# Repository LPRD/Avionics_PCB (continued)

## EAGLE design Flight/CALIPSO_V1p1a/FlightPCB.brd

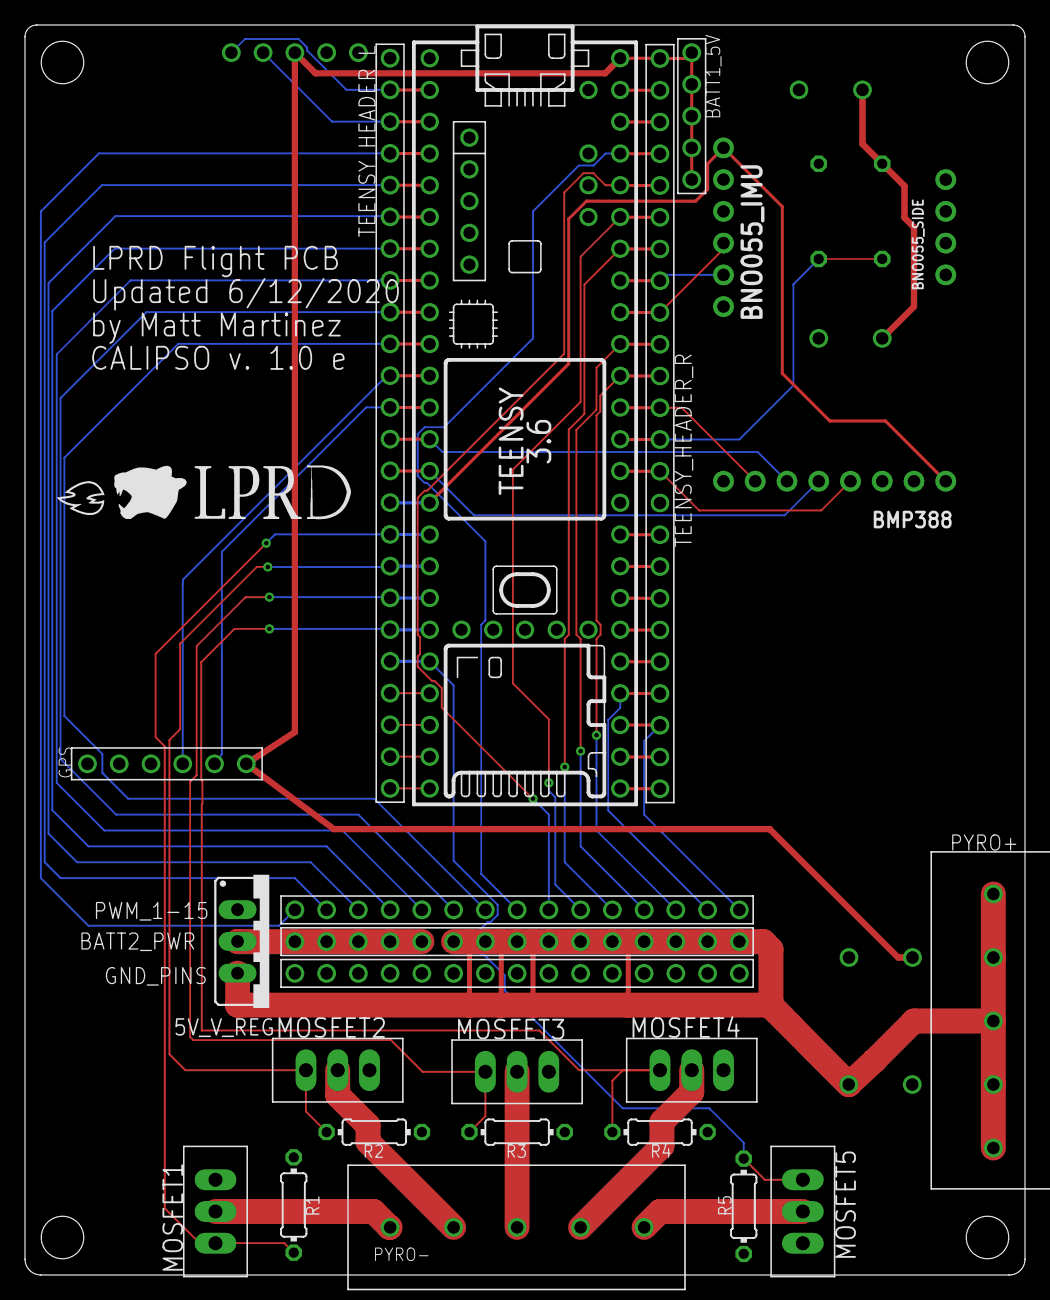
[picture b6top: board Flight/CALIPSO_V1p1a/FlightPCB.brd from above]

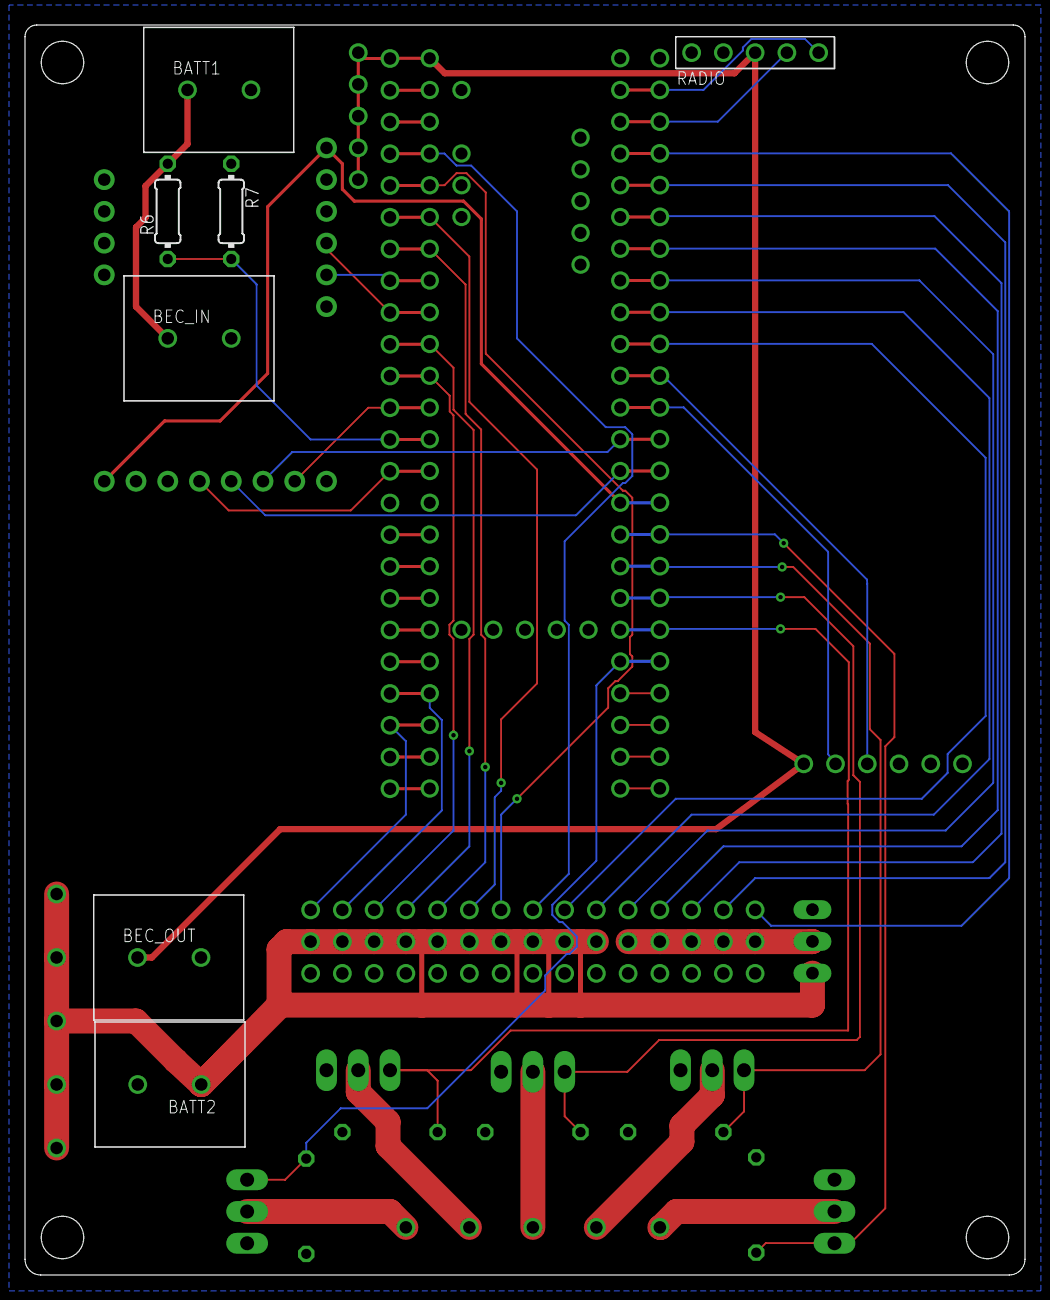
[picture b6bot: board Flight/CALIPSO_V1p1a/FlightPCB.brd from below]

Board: 2 copper layers, 80.0 x 100.0 mm, 31 parts (7 on the bottom side), 55 nets.

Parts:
5V_V_REG: LM1086TO220V; TO220S
BATT1: 2-4S LIPO; TERMINAL_BLOCK_2_PIN_5MM
BATT1_5V: PIN_HEADER_5
BATT2: 2-6S LIPO (>5.6V); TERMINAL_BLOCK_2_PIN_5MM
BATT2_PWR: 1-10=Batt2, 11-15=5V Reg; PIN_HEADER_15
BEC_IN: TERMINAL_BLOCK_2_PIN_5MM
BEC_OUT: TERMINAL_BLOCK_2_PIN_5MM
BMP388: MICROBUILDER_1X08_ROUND
BNO055_IMU: MICROBUILDER_1X06_ROUND
BNO055_SIDE: MICROBUILDER_1X04_ROUND
FLIGHT_COMPUTER: TEENSY_3.5/3.6
GND_PINS: PIN_HEADER_15
GPS: NEO_M8N_GPS_BREAKOUT
MOSFET1, MOSFET2, MOSFET3, MOSFET4, MOSFET5: IRLZ44Z; TO220BH_SIMPLE
PWM_1-15: PIN_HEADER_15
PYRO+: TERMINAL_BLOCK_5_PIN_5MM
PYRO-: TERMINAL_BLOCK_5_PIN_5MM
R1, R2, R3, R4, R5, R6: 10k; 0204/7
R7: 2k; 0204/7
RADIO: RFD900
TEENSY_HEADER_L: PIN_HEADER_24_TEENSY_RAIL
TEENSY_HEADER_R: PIN_HEADER_24_TEENSY_RAIL

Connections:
+3V3: BMP388.1, BNO055_IMU.6, FLIGHT_COMPUTER.3V3, TEENSY_HEADER_L.P10
+5V: BATT1_5V.P1, BATT1_5V.P2, BATT1_5V.P3, BATT1_5V.P4, BATT1_5V.P5, BEC_OUT.P1, FLIGHT_COMPUTER.VIN, GPS.P6, RADIO.3, TEENSY_HEADER_R.P1
+5V/1: 5V_V_REG.2, BATT2_PWR.P11, BATT2_PWR.P12, BATT2_PWR.P13, BATT2_PWR.P14, BATT2_PWR.P15
BATT1_READ_V: FLIGHT_COMPUTER.14/A0, R6.1, R7.2, TEENSY_HEADER_R.P13
BATT1_VCC: BATT1.P1, BEC_IN.P1, R6.2
BMP388_CS0: BMP388.7, FLIGHT_COMPUTER.15/A1, TEENSY_HEADER_R.P12
BMP388_SCK: BMP388.4, FLIGHT_COMPUTER.13/SCK, TEENSY_HEADER_R.P14
BMP388_SDI/MOSI: BMP388.6, FLIGHT_COMPUTER.11/MOSI, TEENSY_HEADER_L.P12
BMP388_SDO/MISO: BMP388.5, FLIGHT_COMPUTER.12/MISO, TEENSY_HEADER_L.P11
BNO055_SCL: BNO055_IMU.2, FLIGHT_COMPUTER.19/A5/SCL, TEENSY_HEADER_R.P8
BNO055_SDA: BNO055_IMU.3, FLIGHT_COMPUTER.18/A4/SDA, TEENSY_HEADER_R.P9
CH1: MOSFET1.D, PYRO-.P1
CH2: MOSFET2.D, PYRO-.P2
CH3: MOSFET3.D, PYRO-.P3
CH4: MOSFET4.D, PYRO-.P4
CH5: MOSFET5.D, PYRO-.P5
GND: 5V_V_REG.1, BATT1.P2, BATT2.P2, BEC_IN.P2, BEC_OUT.P2, BMP388.3, BNO055_IMU.4, FLIGHT_COMPUTER.GND, FLIGHT_COMPUTER.GND2, GND_PINS.P1, GND_PINS.P2, GND_PINS.P3, GND_PINS.P4, GND_PINS.P5, GND_PINS.P6, GND_PINS.P7, GND_PINS.P8, GND_PINS.P9, GND_PINS.P10, GND_PINS.P11, GND_PINS.P12, GND_PINS.P13, GND_PINS.P14, GND_PINS.P15, GPS.P1, MOSFET1.S, MOSFET2.S, MOSFET3.S, MOSFET4.S, MOSFET5.S, R1.2, R2.2, R3.2, R4.2, R5.2, R7.1, RADIO.1, TEENSY_HEADER_L.P24, TEENSY_HEADER_R.P15
GPS_RX: FLIGHT_COMPUTER.10/CS, GPS.P5, TEENSY_HEADER_L.P13
GPS_TX: FLIGHT_COMPUTER.9/CS, GPS.P4, TEENSY_HEADER_L.P14
unnamed: FLIGHT_COMPUTER.AGND, TEENSY_HEADER_R.P2
unnamed: FLIGHT_COMPUTER.3V3_LO, TEENSY_HEADER_R.P3
unnamed: FLIGHT_COMPUTER.32/A13, TEENSY_HEADER_L.P1
unnamed: FLIGHT_COMPUTER.31/A12, TEENSY_HEADER_L.P2
unnamed: FLIGHT_COMPUTER.30, TEENSY_HEADER_L.P3
unnamed: FLIGHT_COMPUTER.29, TEENSY_HEADER_L.P4
unnamed: FLIGHT_COMPUTER.A22/DAC1, TEENSY_HEADER_R.P16
unnamed: FLIGHT_COMPUTER.21/DAC0, TEENSY_HEADER_R.P17
unnamed: FLIGHT_COMPUTER.39/A20, TEENSY_HEADER_R.P18
unnamed: FLIGHT_COMPUTER.38/A19, TEENSY_HEADER_R.P19
unnamed: FLIGHT_COMPUTER.37/A18, TEENSY_HEADER_R.P20
unnamed: FLIGHT_COMPUTER.34/A15, TEENSY_HEADER_R.P23
unnamed: FLIGHT_COMPUTER.33/A14, TEENSY_HEADER_R.P24
PWM2/3: FLIGHT_COMPUTER.3/CANTX, PWM_1-15.P2, TEENSY_HEADER_L.P20
PWM3/4: FLIGHT_COMPUTER.4/CANRX, PWM_1-15.P3, TEENSY_HEADER_L.P19
PWM4/5: FLIGHT_COMPUTER.5, PWM_1-15.P4, TEENSY_HEADER_L.P18
PWM5/6: FLIGHT_COMPUTER.6, PWM_1-15.P5, TEENSY_HEADER_L.P17
PWM6/7: FLIGHT_COMPUTER.7, PWM_1-15.P6, TEENSY_HEADER_L.P16
PWM7/8: FLIGHT_COMPUTER.8, PWM_1-15.P7, TEENSY_HEADER_L.P15
PWM8/23/A9: FLIGHT_COMPUTER.23/A9, PWM_1-15.P8, TEENSY_HEADER_R.P4
PWM9/22/A8: FLIGHT_COMPUTER.22/A8, PWM_1-15.P9, TEENSY_HEADER_R.P5
PWM10/21/A7: FLIGHT_COMPUTER.21/A7, PWM_1-15.P10, TEENSY_HEADER_R.P6
PWM11/20/A6: FLIGHT_COMPUTER.20/A6, PWM_1-15.P11, TEENSY_HEADER_R.P7
PWM12/17/A3: FLIGHT_COMPUTER.17/A3, PWM_1-15.P12, TEENSY_HEADER_R.P10
PWM13/16/A2: FLIGHT_COMPUTER.16/A2, PWM_1-15.P13, TEENSY_HEADER_R.P11
PWM14/36/A17: FLIGHT_COMPUTER.36/A17, PWM_1-15.P14, TEENSY_HEADER_R.P21
PWM15/35/A16: FLIGHT_COMPUTER.35/A16, PWM_1-15.P15, TEENSY_HEADER_R.P22
PWN1/2: FLIGHT_COMPUTER.2, PWM_1-15.P1, TEENSY_HEADER_L.P21
PYRO1: FLIGHT_COMPUTER.24, MOSFET1.G, R1.1, TEENSY_HEADER_L.P9
PYRO2: FLIGHT_COMPUTER.25, MOSFET2.G, R2.1, TEENSY_HEADER_L.P8
PYRO3: FLIGHT_COMPUTER.26, MOSFET3.G, R3.1, TEENSY_HEADER_L.P7
PYRO4: FLIGHT_COMPUTER.27, MOSFET4.G, R4.1, TEENSY_HEADER_L.P6
PYRO5: FLIGHT_COMPUTER.28, MOSFET5.G, R5.1, TEENSY_HEADER_L.P5
RADIO_RX: FLIGHT_COMPUTER.1/TX, RADIO.4, TEENSY_HEADER_L.P22
RADIO_TX: FLIGHT_COMPUTER.0/RX, RADIO.5, TEENSY_HEADER_L.P23
VCC: 5V_V_REG.3, BATT2.P1, BATT2_PWR.P1, BATT2_PWR.P2, BATT2_PWR.P3, BATT2_PWR.P4, BATT2_PWR.P5, BATT2_PWR.P6, BATT2_PWR.P7, BATT2_PWR.P8, BATT2_PWR.P9, BATT2_PWR.P10, PYRO+.P1, PYRO+.P2, PYRO+.P3, PYRO+.P4, PYRO+.P5

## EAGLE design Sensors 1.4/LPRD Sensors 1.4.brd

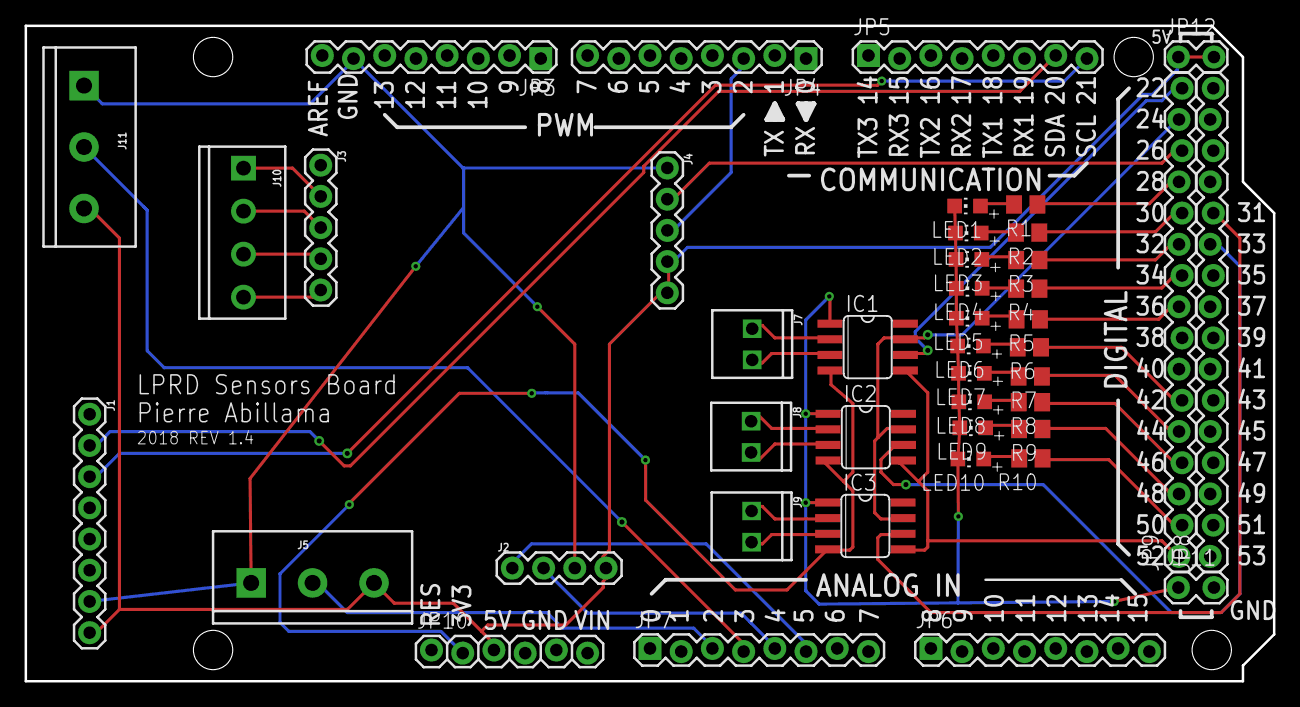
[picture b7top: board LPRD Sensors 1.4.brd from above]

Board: 2 copper layers, 101.6 x 53.3 mm, 45 parts (0 on the bottom side), 46 nets.

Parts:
IC1, IC2, IC3: MAX31855; SO08
J1: 1X08
J2: 1X04
J3, J4: 1X05
J5, J11: SCREWTERMINAL-5MM-3
J7, J8, J9: 1X02_2.54_SCREWTERM
J10: SCREWTERMINAL-3.5MM-4
JP3, JP4, JP5, JP6, JP7: 1X08_LOCK
JP8, JP9: M16LOCK; 1X16_LOCK
JP10: 1X06_LOCK
JP11, JP12: 1X02_LOCK
LED1, LED2, LED3, LED4, LED5, LED6, LED7, LED8, LED9, LED10: CHIP-LED0805
R1, R2, R3, R4, R5, R6, R7, R8, R9, R10: 1000; R0805
U$1: UMNLOGO
U$2: LPRDLOGO

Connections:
3.3V: IC1.4, IC2.4, IC3.4, JP10.2
5V: J1.8, J2.4, J4.4, J4.5, J5.3, J11.3, JP10.3, JP12.1, JP12.2
A+/GREEN: J3.2, J10.1
A-/WHITE: J3.3, J10.2
E+/RED: J3.5, J10.4
E-/BLACK: J3.4, J10.3
FORCE_CLK: J4.2, JP9.14
FORCE_DAT: J4.3, JP4.3
FORCE_LED: JP9.10, R4.1
GND: IC1.1, IC2.1, IC3.1, J1.7, J2.3, J4.1, J5.1, J11.1, JP3.7, JP10.4, JP10.5, JP11.1, JP11.2, LED1.C, LED2.C, LED3.C, LED4.C, LED5.C, LED6.C, LED7.C, LED8.C, LED9.C, LED10.C
MAXCLK: IC1.5, IC2.5, IC3.5, JP9.1
MAXCS1: IC1.6, JP9.16
MAXCS2: IC2.6, JP8.11
MAXCS3: IC3.6, JP8.12
MAXDO: IC1.7, IC2.7, IC3.7, JP9.15
unnamed: LED1.A, R1.2
unnamed: LED2.A, R2.2
unnamed: LED3.A, R3.2
unnamed: LED4.A, R4.2
unnamed: LED5.A, R5.2
unnamed: LED6.A, R6.2
unnamed: LED7.A, R7.2
unnamed: IC1.2, J7.P2
unnamed: IC1.3, J7.P1
unnamed: IC2.2, J8.P2
unnamed: IC2.3, J8.P1
unnamed: IC3.2, J9.P2
unnamed: IC3.3, J9.P1
unnamed: LED8.A, R8.2
unnamed: LED9.A, R9.2
unnamed: LED10.A, R10.2
PRESSURE1_LED: JP9.9, R5.1
PRESSURE2_LED: JP9.2, R10.1
SCL: J1.3, JP5.8
SDA: J1.2, JP5.7
STATE_LED: JP9.6, R6.1
STATUS_LED: JP9.5, R7.1
TEMP1_LED: JP9.4, R8.1
TEMP2_LED: JP9.3, R9.1
THERMO1_LED: JP9.13, R1.1
THERMO2_LED: JP9.12, R2.1
THERMO3_LED: JP9.11, R3.1
VOUT_PRESSURE_1: J5.2, JP7.3
VOUT_PRESSURE_2: J11.2, JP7.4
VOUT_TEMPERATURE_1: J2.2, JP7.5
VOUT_TEMPERATURE_2: J2.1, JP7.6

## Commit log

2018-04-09 Fixed typo
2018-04-09 Fixed SDA and SCL, fixed thermo amp 3.3
2018-04-10 Added Valve control board V2.1
2018-10-13 Updated valve board files and included gerber files
2019-09-19 Archiving old PCBs, add new version
2019-09-19 Move some components, add version number to silkscreen
2019-09-19 Adding libraries
2019-09-19 Fix voltage regulator in library
2019-09-19 Fix voltage regulators on board
2019-09-20 More fixes/tweaks
2019-09-20 Add logo
2019-09-28 Add .gitignore
2019-09-28 Adding copied sensors PCB
2019-09-28 Add TODO file
2019-10-05 Removed thermocouples, added JSTs
2019-10-05 Test commit
2019-10-05 Updated Schematic, pins now aligned and connected
2019-10-05 Rewired force JST mount
2019-10-05 Refixed names on load cell JST
2019-10-05 Finished routing, added accelerometer LED
    UMN Logo is on wrong side, but such is life.
2019-10-05 Rearranged load cell seat, adressed errors
2019-10-06 Misc. minor tweaks to routing, layout and labels
2019-10-07 Some changes that I forgot to push yesterday
2019-10-11 Final tweaks and minor fixes
2019-10-11 Fix silkscreen to use vector fonts
2019-10-11 Gerber files for version to order
2019-11-02 Fix mistakes in sensors schematic
2019-11-02 Fix net naming error
2019-11-09 Update version number
2019-11-09 Fix misc. problems found by DRC
2019-11-09 Adding gerber files
2019-11-26 Fix backwards pressure pin net names
2020-02-06 Add some notes on stuff to change
2020-02-29 Fix 5V pins in Mega shield library that were incorrectly labled as GND
2020-03-01 Update schematic for valve board
2020-03-01 Add MOSFET to LPRD_RELAY library
2020-03-01 Fix schematic errors, finish board layout
2020-03-01 Increase trace width between FET drains and output connector
2020-03-01 Add direction indication to JST connector silkscreen in library
2020-03-01 Redesign sensors PCB - remove LEDs and add additional components
2020-03-01 Added new FlightPCB v1.0d
    Added new FlightPCB v1.0d to the Avionics_PCB repository
2020-03-01 Change header package to remove staggered pins
2020-03-03 Some minor tweaks to the layout
2020-03-05 Add pin numbers to valve pin selection jumper header
2020-03-05 More final tweaks to valve board layout
2020-03-05 Add generated geber files for both boards
2020-03-06 Fix thermocouple amp spacing
2020-03-06 Actual final version of sensors board
2020-03-24 Some minor adjustments to sensors board layout for future revisions, based on lessons learned from populating v3.0 (not routed yet)
2020-03-26 Remove partial broken routing
2020-03-26 Remove diodes, fix some slight layout issues
2020-03-26 Fix MUX silkscreen layer
2020-06-14 Fixes to Flight PCB
    Fixed hole sizing/placement, BEC clearance, GPS clearance, terminal block clearance, resistor hole spacing. Minor silkscreen adjustments
2020-07-19 File System Reorganization
    Unpushed changes from 10 days ago. 6/14 has the actual changes to the board I think. This push just has changes to the folders/names so that older revisions can be found.
2020-09-22 CALIPSO V2.0 Initial Commit
    initial version of the new flight computer design is done, will likely make make fixes before ordering any PCBs
2020-10-11 MFG Files
    Includes PDFs and CSV files for parts... PCB file is no longer ready to order as it has to be re-routed
2021-01-28 Unsaved changes after 10/11/2020
    changes that I made after 10/11/2020. I don't recall what all the changes are, but I will look soon.
2022-03-29 Added 2021 changes
    added changes for V3 Hardware that were done in 2021
